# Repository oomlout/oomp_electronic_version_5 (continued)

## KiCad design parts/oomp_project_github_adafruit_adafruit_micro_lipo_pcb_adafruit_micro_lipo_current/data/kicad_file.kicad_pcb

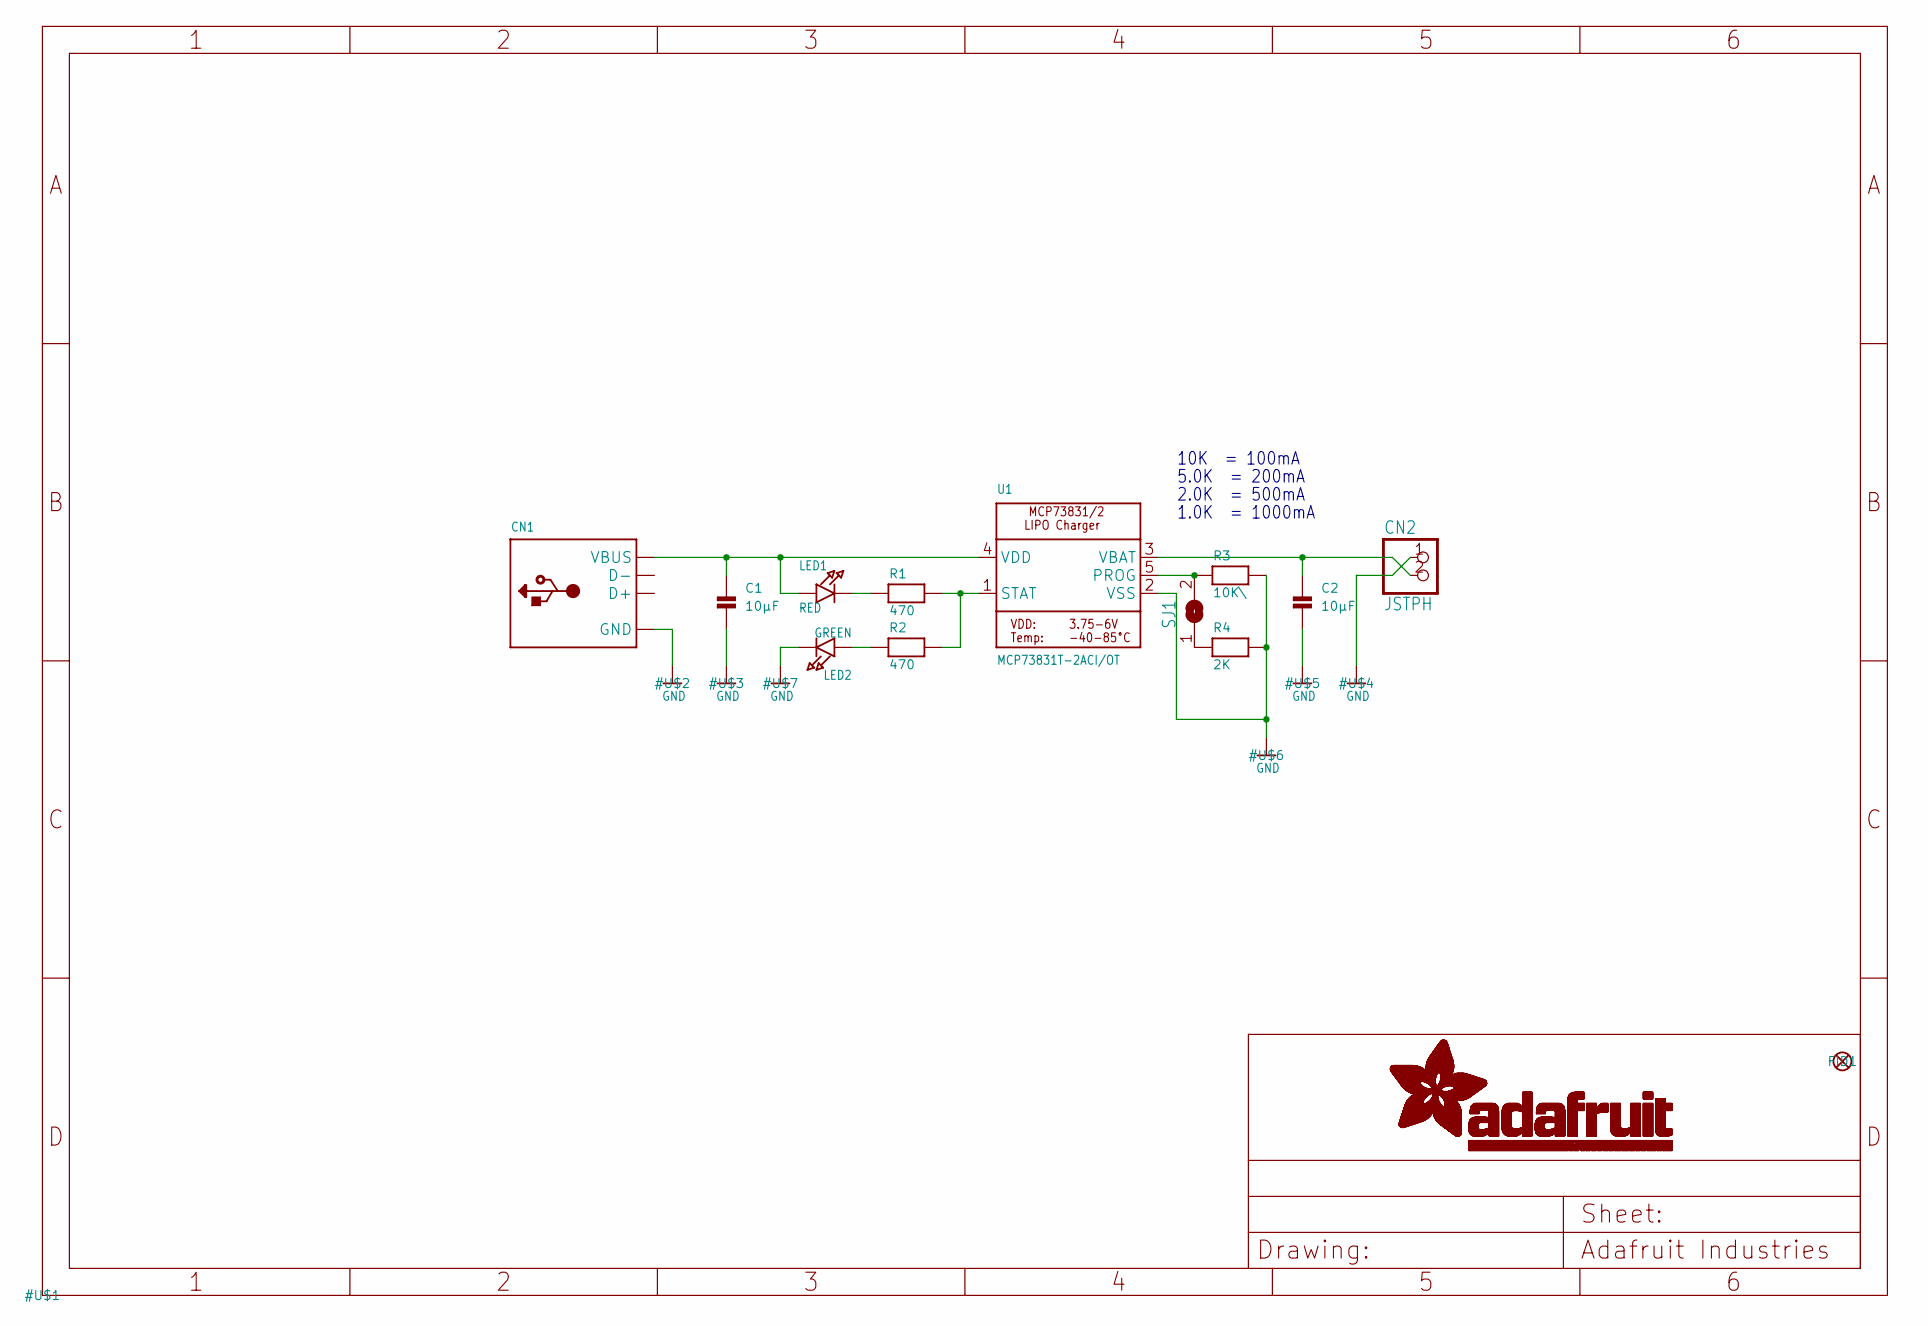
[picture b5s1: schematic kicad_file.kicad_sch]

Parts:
C1, C2: 10µF; 0805
CN1: USB_TYPEAPCB; USBA_PCB
CN2: JSTPH; JSTPH2
FID1: FIDUCIAL""; FIDUCIAL_1MM
LED1: RED; CHIPLED_0805
LED2: GREEN; CHIPLED_0805
R1, R2: 470; 0805
R3: 10K\; 0805
R4: 2K; 0805
SJ1: SOLDERJUMPER; SOLDERJUMPER_ARROW_NOPASTE
U1: MCP73831T-2ACI/OT; SOT23-5

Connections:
GND: C1.2, C2.2, CN1.GND, CN2.1, LED2.C, R3.2, R4.2, U1.2 (VSS)
unnamed: LED1.C, R1.1
unnamed: R1.2, R2.2, U1.1 (STAT)
unnamed: R4.1, SJ1.1
unnamed: R3.1, SJ1.2, U1.5 (PROG)
unnamed: LED2.A, R2.1
VBAT: C2.1, CN2.2, U1.3 (VBAT)
VDD: C1.1, CN1.VCC (VBUS), LED1.A, U1.4 (VDD)

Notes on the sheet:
5.0K = 200mA
10K = 100mA
1.0K = 1000mA
2.0K = 500mA

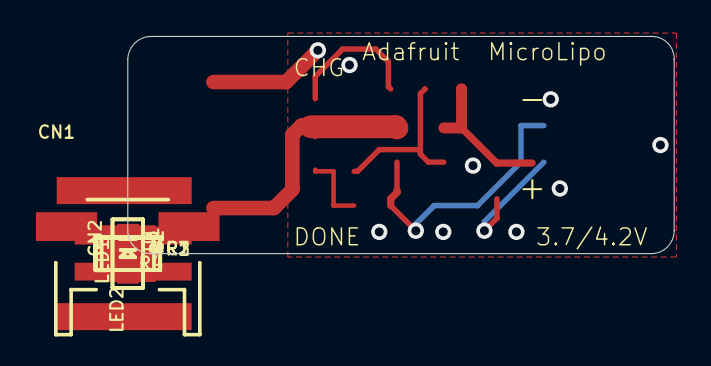
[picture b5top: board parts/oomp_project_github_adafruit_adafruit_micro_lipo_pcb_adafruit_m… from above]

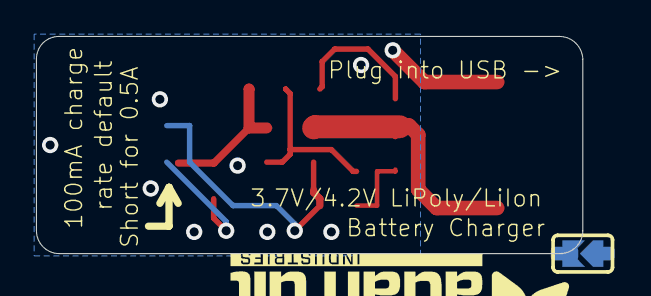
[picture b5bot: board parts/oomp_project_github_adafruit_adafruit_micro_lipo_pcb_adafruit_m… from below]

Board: 2 copper layers, 30.4 x 12.1 mm, 14 parts (2 on the bottom side), 8 nets.

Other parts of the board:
U$8: ADAFRUIT_TEXT_20MM

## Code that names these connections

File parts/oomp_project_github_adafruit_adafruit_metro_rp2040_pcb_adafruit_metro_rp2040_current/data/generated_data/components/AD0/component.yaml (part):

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      connected_to:
      - reference: IC2
        pin_number: '38'
        pin_name: GPIO26/AD0
    - number: '2'
      name: '2'
      electrical_type: passive
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      connected_to:
      - reference: IC2
        pin_number: '39'
        pin_name: GPIO27/AD1
    - number: '3'
      name: '3'
      electrical_type: passive
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      connected_to:
      - reference: IC2
        pin_number: '40'
        pin_name: GPIO28/AD2
    - number: '4'
      name: '4'
      electrical_type: passive
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      connected_to:
      - reference: IC2
        pin_number: '41'
        pin_name: GPIO29/AD3
    - number: '5'
      name: '5'
      electrical_type: passive
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      connected_to:
      - reference: IC2
        pin_number: '36'
        pin_name: GPIO24
    - number: '6'
      name: '6'
      electrical_type: passive
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      connected_to:
      - reference: IC2
        pin_number: '37'
        pin_name: GPIO25
    size:
      local_graphics:
        measurement: symbol graphics only; excludes pins, properties, and text
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  connected_components:
  - reference: IC2
    pin_number: '36'
    pin_name: GPIO24
  - reference: IC2
    pin_number: '37'
    pin_name: GPIO25
  - reference: IC2
    pin_number: '38'
    pin_name: GPIO26/AD0
  - reference: IC2
    pin_number: '39'
    pin_name: GPIO27/AD1
  - reference: IC2
    pin_number: '40'
    pin_name: GPIO28/AD2
  - reference: IC2
    pin_number: '41'
    pin_name: GPIO29/AD3
pcb:
  reference: AD0
  value: '20609'
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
